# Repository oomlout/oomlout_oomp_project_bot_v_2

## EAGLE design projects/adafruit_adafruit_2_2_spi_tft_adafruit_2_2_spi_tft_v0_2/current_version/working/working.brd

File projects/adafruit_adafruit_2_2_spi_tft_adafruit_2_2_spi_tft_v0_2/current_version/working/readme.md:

# adafruit_2_2_spi_tft
 
## summary 
* id: adafruit_adafruit_2_2_spi_tft_adafruit_2_2_spi_tft_v0_2
* user: adafruit
* name: adafruit_2_2_spi_tft
* board: adafruit_2_2_spi_tft_v0_2
* repo: https://github.com/adafruit/Adafruit-2.2-SPI-TFT

* src_file_repo_sch: 
* src_file_repo_sch_link: https://github.com/adafruit/Adafruit-2.2-SPI-TFT/tree/master/
* full details link: https://github.com/oomlout/oomlout_oomp_project_bot_v_2/tree/main/projects/adafruit_adafruit_2_2_spi_tft_adafruit_2_2_spi_tft_v0_2/current_version/working  

## pcb  

[board (pdf)](working.pdf)

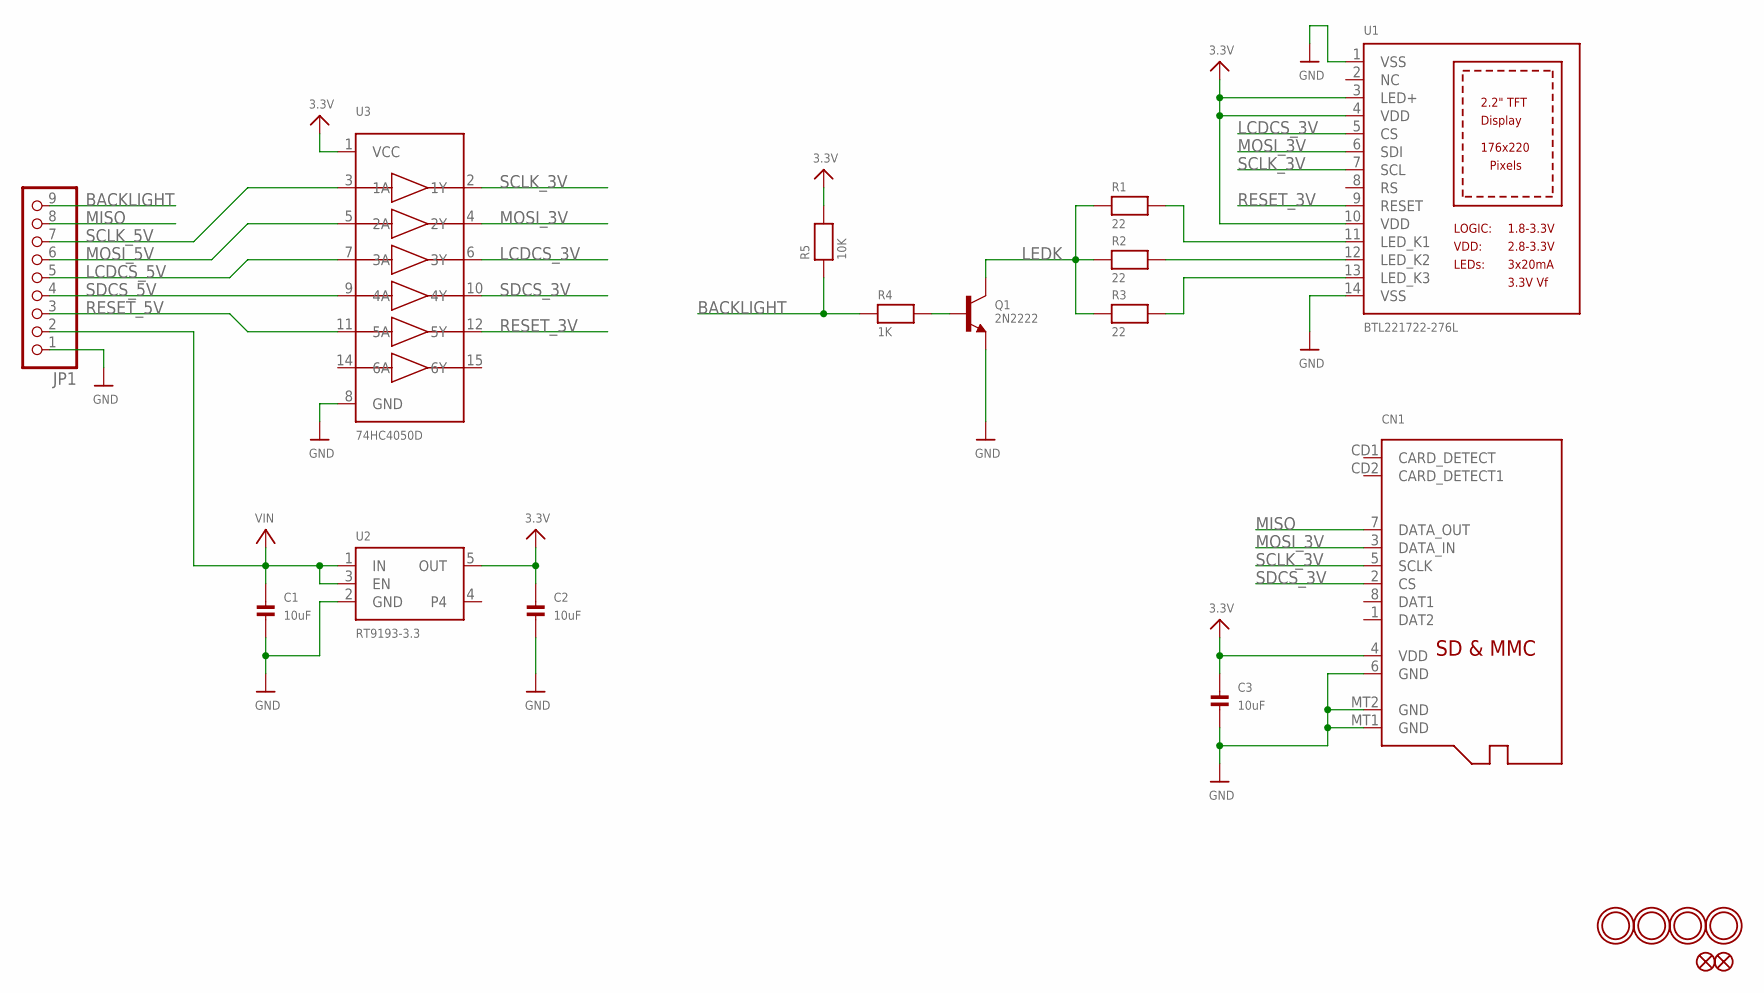
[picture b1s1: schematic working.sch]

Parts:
C1, C2, C3: 10uF; 0805
CN1: MICROSD
FID1, FID2: FIDUCIAL""; FIDUCIAL_1MM
JP1: HEADER-1X970MIL; 1X09_ROUND_70
Q1: 2N2222; SOT23-WIDE
R1, R2, R3: 22; 0805
R4: 1K; 0805
R5: 10K; 0805
U1: BTL221722-276L
U2: RT9193-3.3; SOT23-5
U3: 74HC4050D; SOIC16
U$2, U$3, U$4, U$5: MOUNTINGHOLE2.5; MOUNTINGHOLE_2.5_PLATED

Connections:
3.3V: C2.1, C3.1, CN1.4 (VDD), R5.2, U1.3 (LED+), U1.4 (VDD), U1.10 (VDD), U2.5 (OUT), U3.1 (VCC)
BACKLIGHT: JP1.9, R4.1, R5.1
GND: C1.2, C2.2, C3.2, CN1.6 (GND), CN1.MT1 (GND), CN1.MT2 (GND), JP1.1, Q1.2 (E), U1.1 (VSS), U1.14 (VSS), U2.2 (GND), U3.8 (GND)
LCDCS_3V: U1.5 (CS), U3.6 (3Y)
LCDCS_5V: JP1.5, U3.7 (3A)
LEDK: Q1.3 (C), R1.1, R2.1, R3.1
MISO: CN1.7 (DATA_OUT), JP1.8
MOSI_3V: CN1.3 (DATA_IN), U1.6 (SDI), U3.4 (2Y)
MOSI_5V: JP1.6, U3.5 (2A)
unnamed: R1.2, U1.11 (LED_K1)
unnamed: R2.2, U1.12 (LED_K2)
unnamed: R3.2, U1.13 (LED_K3)
unnamed: Q1.1 (B), R4.2
RESET_3V: U1.9 (RESET), U3.12 (5Y)
RESET_5V: JP1.3, U3.11 (5A)
SCLK_3V: CN1.5 (SCLK), U1.7 (SCL), U3.2 (1Y)
SCLK_5V: JP1.7, U3.3 (1A)
SDCS_3V: CN1.2 (CS), U3.10 (4Y)
SDCS_5V: JP1.4, U3.9 (4A)
VIN: C1.1, JP1.2, U2.1 (IN), U2.3 (EN)

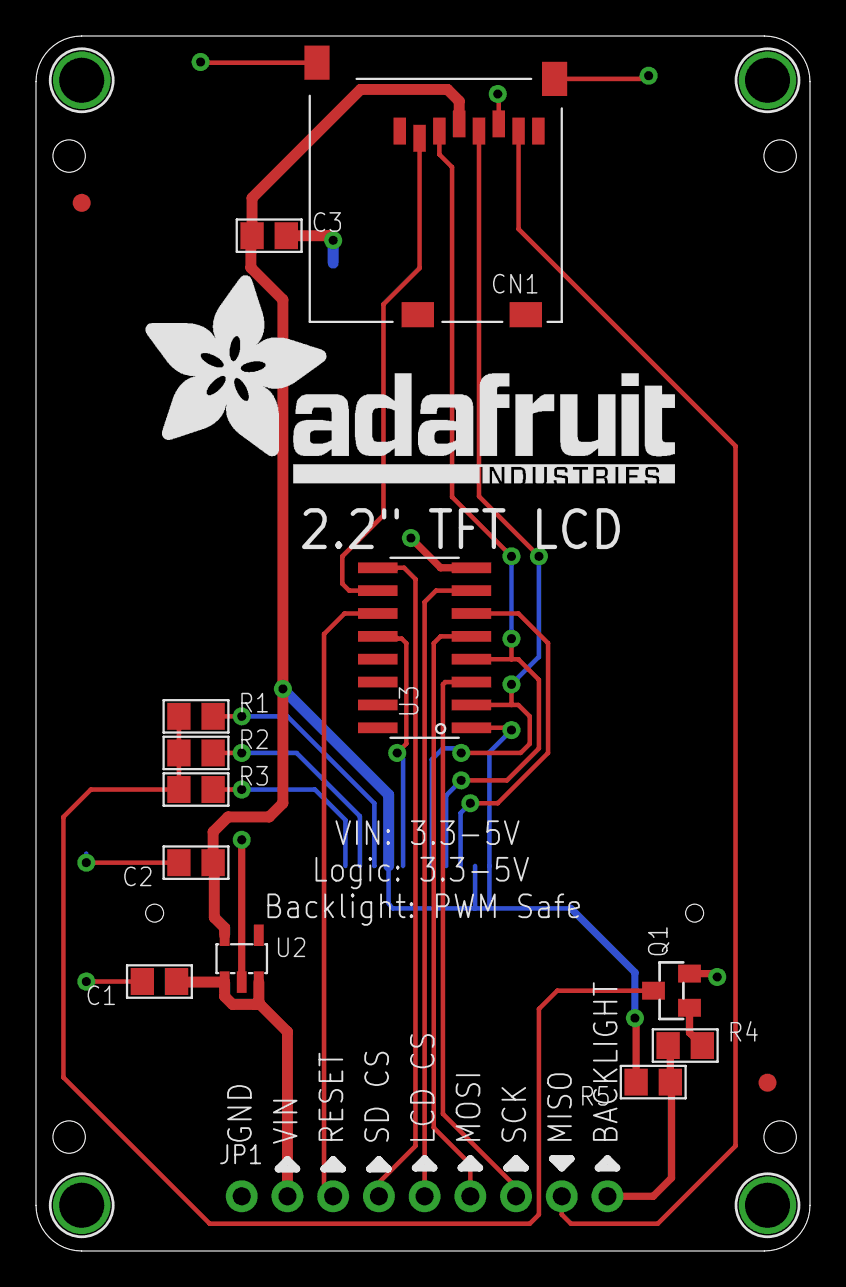
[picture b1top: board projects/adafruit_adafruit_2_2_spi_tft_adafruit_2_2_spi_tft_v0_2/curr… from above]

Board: 2 copper layers, 43.0 x 67.5 mm, 21 parts (1 on the bottom side), 20 nets.

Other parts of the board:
U$20: ADAFRUIT_TEXT_30MM

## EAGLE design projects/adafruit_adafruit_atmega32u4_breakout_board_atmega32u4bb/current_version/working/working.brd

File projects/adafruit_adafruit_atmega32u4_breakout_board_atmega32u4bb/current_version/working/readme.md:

# adafruit_atmega32u4_breakout_board
 
## summary 
* id: adafruit_adafruit_atmega32u4_breakout_board_atmega32u4bb
* user: adafruit
* name: adafruit_atmega32u4_breakout_board
* board: atmega32u4bb
* repo: https://github.com/adafruit/Adafruit_Atmega32u4_Breakout_Board

* src_file_repo_sch: 
* src_file_repo_sch_link: https://github.com/adafruit/Adafruit_Atmega32u4_Breakout_Board/tree/master/
* full details link: https://github.com/oomlout/oomlout_oomp_project_bot_v_2/tree/main/projects/adafruit_adafruit_atmega32u4_breakout_board_atmega32u4bb/current_version/working  

## pcb  

[board (pdf)](working.pdf)

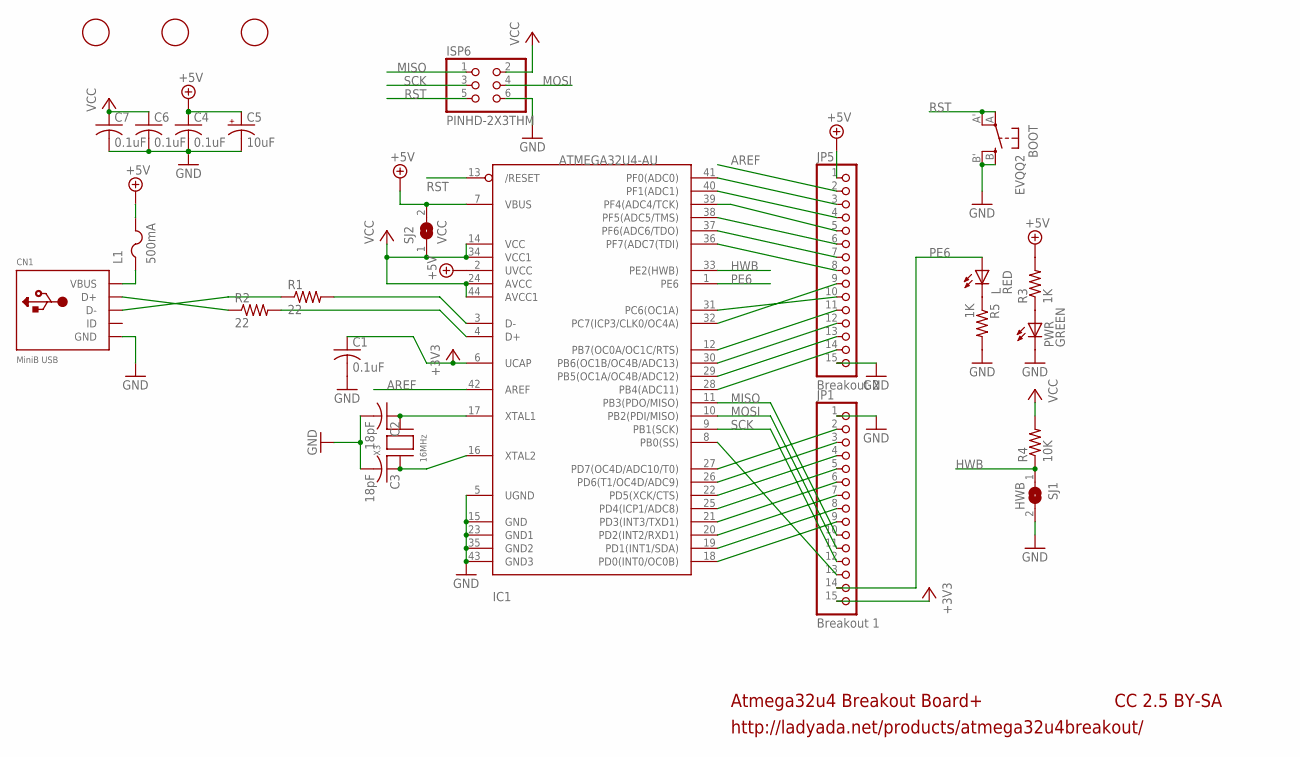
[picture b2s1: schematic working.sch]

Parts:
BOOT: EVQQ2; EVQ-Q2
C1, C4, C6, C7: 0.1uF; C0805K
C2, C3: 18pF; C0805K
C5: 10uF; A/3216-18R
CN1: MiniB USB; USB-MINIB
IC1: ATMEGA32U4-AU; TQFP44
ISP6: PINHD-2X3THM; ISP6
JP1: Breakout 1; 1X15-CB
JP5: Breakout 2; 1X15-CB
L: RED; CHIPLED_0805
L1: 500mA; R1206
PWR: GREEN; CHIPLED_0805
R1, R2: 22; R0805
R3, R5: 1K; R0805
R4: 10K; R0805
SJ1: HWB; SJ
SJ2: VCC; SJ
U$1, U$2, U$6: FIDUCIAL; FIDUCIAL_1MM
X3: 16MHz; NX5032

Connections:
+3V3: C1.1, IC1.6 (UCAP), JP1.15
+5V: C4.1, C5.+, IC1.2 (UVCC), IC1.7 (VBUS), JP5.1, L1.2, R3.2, SJ2.2
AREF: IC1.42 (AREF), JP5.2
GND: BOOT.B (S), BOOT.B' (S1), C1.2, C2.2, C3.2, C4.2, C5.-, C6.2, C7.2, CN1.GND, IC1.5 (UGND), IC1.15 (GND), IC1.23 (GND1), IC1.35 (GND2), IC1.43 (GND3), ISP6.6, JP1.1, JP5.15, PWR.C, R5.2, SJ1.2
HWB: IC1.33 (PE2(HWB)), R4.1, SJ1.1
MISO: IC1.11 (PB3(PDO/MISO)), ISP6.1, JP1.10
MOSI: IC1.10 (PB2(PDI/MISO)), ISP6.4, JP1.11
unnamed: PWR.A, R3.1
unnamed: CN1.D+, R2.1
unnamed: IC1.3 (D-), R1.2
unnamed: IC1.4 (D+), R2.2
unnamed: CN1.D-, R1.1
unnamed: C2.1, IC1.17 (XTAL1), X3.P$2
unnamed: C3.1, IC1.16 (XTAL2), X3.P$1
unnamed: L.C, R5.1
PB0: IC1.8 (PB0(SS)), JP1.13
PB4: IC1.28 (PB4(ADC11)), JP5.14
PB5: IC1.29 (PB5(OC1A/OC4B/ADC12)), JP5.13
PB6: IC1.30 (PB6(OC1B/OC4B/ADC13)), JP5.12
PB7: IC1.12 (PB7(OC0A/OC1C/RTS)), JP5.11
PC6: IC1.31 (PC6(OC1A)), JP5.10
PC7: IC1.32 (PC7(ICP3/CLK0/OC4A)), JP5.9
PD0: IC1.18 (PD0(INT0/OC0B)), JP1.9
PD1: IC1.19 (PD1(INT1/SDA)), JP1.8
PD2: IC1.20 (PD2(INT2/RXD1)), JP1.7
PD3: IC1.21 (PD3(INT3/TXD1)), JP1.6
PD4: IC1.25 (PD4(ICP1/ADC8)), JP1.5
PD5: IC1.22 (PD5(XCK/CTS)), JP1.4
PD6: IC1.26 (PD6(T1/OC4D/ADC9)), JP1.3
PD7: IC1.27 (PD7(OC4D/ADC10/T0)), JP1.2
PE6: IC1.1 (PE6), JP1.14, L.A
PF0: IC1.41 (PF0(ADC0)), JP5.3
PF1: IC1.40 (PF1(ADC1)), JP5.4
PF4: IC1.39 (PF4(ADC4/TCK)), JP5.5
PF5: IC1.38 (PF5(ADC5/TMS)), JP5.6
PF6: IC1.37 (PF6(ADC6/TDO)), JP5.7
PF7: IC1.36 (PF7(ADC7(TDI)), JP5.8
RST: BOOT.A, BOOT.A' (P1), IC1.13 (/RESET), ISP6.5
SCK: IC1.9 (PB1(SCK)), ISP6.3, JP1.12
VBUS: CN1.VBUS, L1.1
VCC: C6.1, C7.1, IC1.14 (VCC), IC1.24 (AVCC), IC1.34 (VCC1), IC1.44 (AVCC1), ISP6.2, R4.2, SJ2.1

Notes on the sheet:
Atmega32u4 Breakout Board+
http://ladyada.net/products/atmega32u4breakout/
CC 2.5 BY-SA

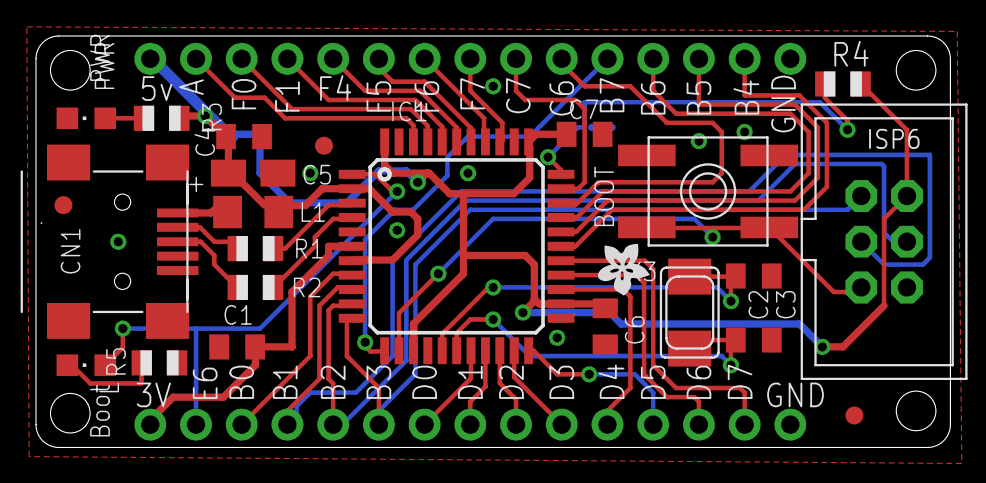
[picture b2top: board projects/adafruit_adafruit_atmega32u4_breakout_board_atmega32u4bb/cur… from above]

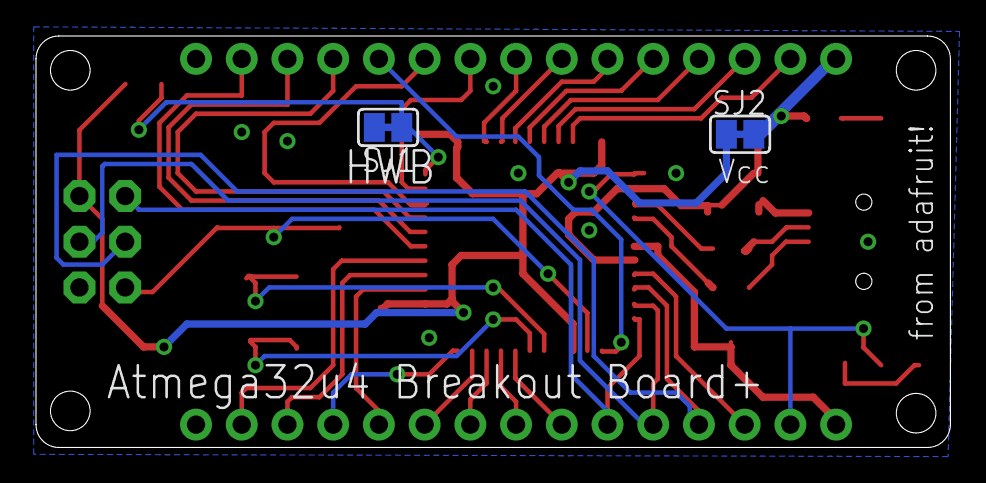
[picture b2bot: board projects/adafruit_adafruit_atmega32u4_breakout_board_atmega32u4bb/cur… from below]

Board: 2 copper layers, 50.8 x 22.9 mm, 28 parts (2 on the bottom side), 41 nets.

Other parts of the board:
U$4: ADAFRUIT200MIL

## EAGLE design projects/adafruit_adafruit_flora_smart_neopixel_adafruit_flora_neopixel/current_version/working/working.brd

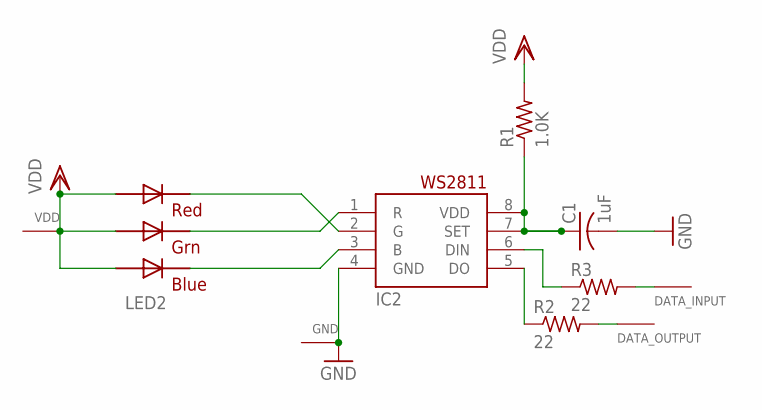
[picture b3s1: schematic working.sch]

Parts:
C1: 1uF; C0805K
DATA_INPUT: SEWTAP0.5IN; SEWINGTAP_0.5
DATA_OUTPUT: SEWTAP0.5IN; SEWINGTAP_0.5
GND: SEWTAP0.5IN; SEWINGTAP_0.5
IC2: WS2811-SOP8; SO08-SKINNYPADS
LED2: RGBLED5050
R1: 1.0K; R0805
R2, R3: 22; R0805
VDD: SEWTAP0.5IN; SEWINGTAP_0.5

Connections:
GND: C1.2, GND.TAP, IC2.4 (GND)
unnamed: IC2.3 (B), LED2.4 (BLUE_C)
unnamed: IC2.2 (G), LED2.5 (RED_C)
unnamed: IC2.1 (R), LED2.6 (GREEN_C)
unnamed: IC2.6 (DIN), R3.1
unnamed: IC2.5 (DO), R2.1
unnamed: DATA_INPUT.TAP, R3.2
unnamed: DATA_OUTPUT.TAP, R2.2
unnamed: C1.1, IC2.7 (SET), IC2.8 (VDD), R1.1
VDD: LED2.1 (GREEN_A), LED2.2 (RED_A), LED2.3 (BLUE_A), R1.2, VDD.TAP

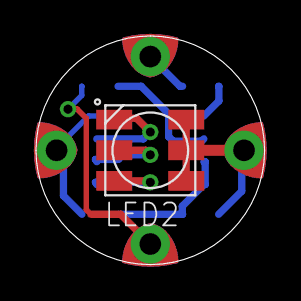
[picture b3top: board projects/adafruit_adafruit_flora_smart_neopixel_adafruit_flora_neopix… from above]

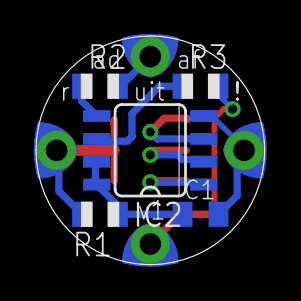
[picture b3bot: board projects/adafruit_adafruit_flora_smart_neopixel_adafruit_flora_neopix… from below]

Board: 2 copper layers, 12.7 x 12.7 mm, 10 parts (5 on the bottom side), 10 nets.

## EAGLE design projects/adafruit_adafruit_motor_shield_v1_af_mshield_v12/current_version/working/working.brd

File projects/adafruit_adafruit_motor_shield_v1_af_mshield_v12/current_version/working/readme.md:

# adafruit_motor_shield_v1
 
## summary 
* id: adafruit_adafruit_motor_shield_v1_af_mshield_v12
* user: adafruit
* name: adafruit_motor_shield_v1
* board: af_mshield_v12
* repo: https://github.com/adafruit/Adafruit_Motor-Shield-v1

* src_file_repo_sch: 
* src_file_repo_sch_link: https://github.com/adafruit/Adafruit_Motor-Shield-v1/tree/master/
* full details link: https://github.com/oomlout/oomlout_oomp_project_bot_v_2/tree/main/projects/adafruit_adafruit_motor_shield_v1_af_mshield_v12/current_version/working  

## schematic  
  
[schematic (pdf)](working_schematic.pdf) 

## pcb  

[board (pdf)](working.pdf)  

## bom_schematic
no data

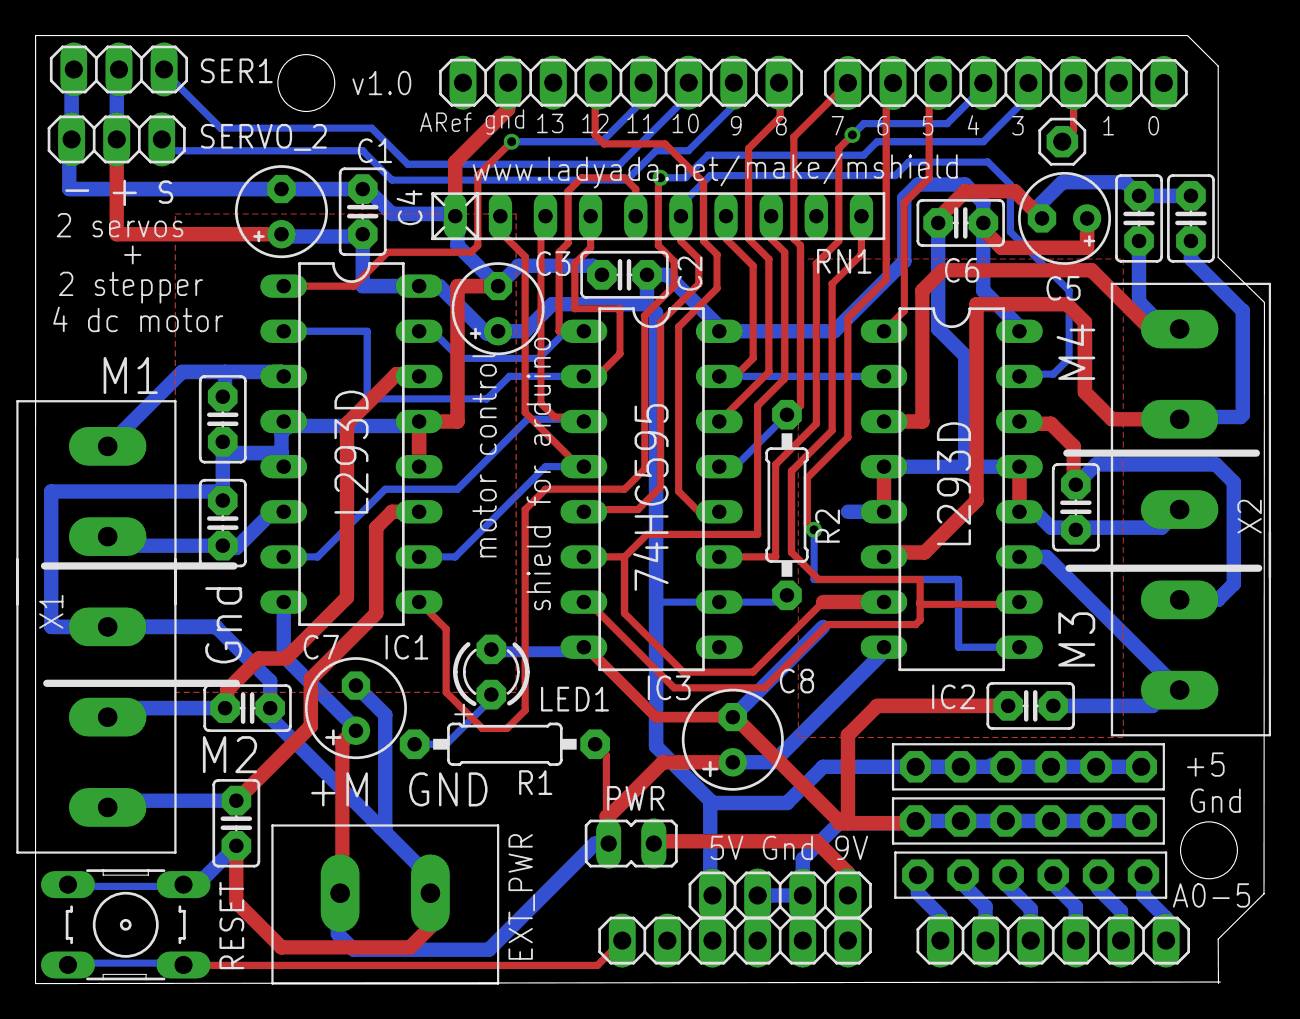
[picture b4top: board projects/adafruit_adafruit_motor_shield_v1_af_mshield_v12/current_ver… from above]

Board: 2 copper layers, 69.2 x 53.4 mm, 39 parts (0 on the bottom side), 39 nets.

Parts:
C1, C3, C5: 100uF/6V; E2,5-5
C2, C4, C10, C11, C12, C13, C20, C21, C22, C23: 0.1uF; C025-025X050
C6: C025-025X050
C7, C8: 100uF/16V; E2,5-6
EXT_PWR: PINHEAD; TERMBLOCK508
IC1, IC2: DIL16
IC3: 74HCT595N; DIL16
J1, J3: 1X08
JP1, JP2: 1X06
JP3: 1X01
JP4: 1X04
JP5, JP8, JP10: 1X06-BIG
LED1: LED3MM
PWR: JP1
R1: 0207/10
R2: 10k; 0207/10
RESET: Reset; B3F-10XX
RN1: RN-10
SER1: 1X03
SERVO_2: 1X03
X1, X2: TERM5; TERM1X5

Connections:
9V: JP1.6, JP4.4, PWR.1
DIR_CLK: IC3.11, J1.5
DIR_EN: IC3.13, J1.8, R2.2
DIR_LATCH: IC3.12, J3.5
DIR_SER: IC3.14, J3.1
GND: C1.-, C2.2, C3.-, C4.2, C5.-, C6.2, C7.-, C8.-, C10.2, C11.2, C12.2, C13.2, C20.2, C21.2, C22.2, C23.2, EXT_PWR.P$4, IC1.4, IC1.5, IC1.12, IC1.13, IC2.4, IC2.5, IC2.12, IC2.13, IC3.8, J3.7, JP1.4, JP1.5, JP4.2, JP4.3, JP10.1, JP10.2, JP10.3, JP10.4, JP10.5, JP10.6, LED1.K, RESET.1, RESET.2, RN1.1, SER1.3, SERVO_2.3, X1.P3, X2.P3
M1A: IC1.2, IC3.2, RN1.4
M1B: IC1.7, IC3.3, RN1.3
M2A: IC1.15, IC3.1, RN1.5
M2B: IC1.10, IC3.4, RN1.2
M3A: IC2.2, IC3.15, RN1.7
M3B: IC2.7, IC3.6, RN1.8
M4A: IC2.15, IC3.5, RN1.6
M4B: IC2.10, IC3.7, RN1.10
unnamed: C13.1, IC1.3, X1.P1
unnamed: JP2.1, JP5.1
unnamed: JP2.2, JP5.2
unnamed: JP2.3, JP5.3
unnamed: JP2.4, JP5.4
unnamed: JP2.5, JP5.5
unnamed: C23.1, IC2.3, X2.P5
unnamed: C22.1, IC2.6, X2.P4
unnamed: C20.1, IC2.11, X2.P1
unnamed: J1.3, JP3.1
unnamed: JP2.6, JP5.6
unnamed: C21.1, IC2.14, X2.P2
unnamed: C12.1, IC1.6, X1.P2
unnamed: C10.1, IC1.11, X1.P5
unnamed: C11.1, IC1.14, X1.P4
unnamed: LED1.A, R1.1
PWM0A: IC2.9, J1.7
PWM0B: IC2.1, J1.6
PWM1A: J3.2, SERVO_2.1
PWM1B: J3.3, SER1.1
PWM2A: IC1.1, J3.4
PWM2B: IC1.9, J1.4
RESET: JP1.1, RESET.3, RESET.4
V+: C7.+, C8.+, EXT_PWR.P$3, IC1.8, IC2.8, PWR.2, R1.2
VCC: C1.+, C2.1, C3.+, C4.1, C5.+, C6.1, IC1.16, IC2.16, IC3.10, IC3.16, JP1.3, JP4.1, JP8.1, JP8.2, JP8.3, JP8.4, JP8.5, JP8.6, R2.1, SER1.2, SERVO_2.2

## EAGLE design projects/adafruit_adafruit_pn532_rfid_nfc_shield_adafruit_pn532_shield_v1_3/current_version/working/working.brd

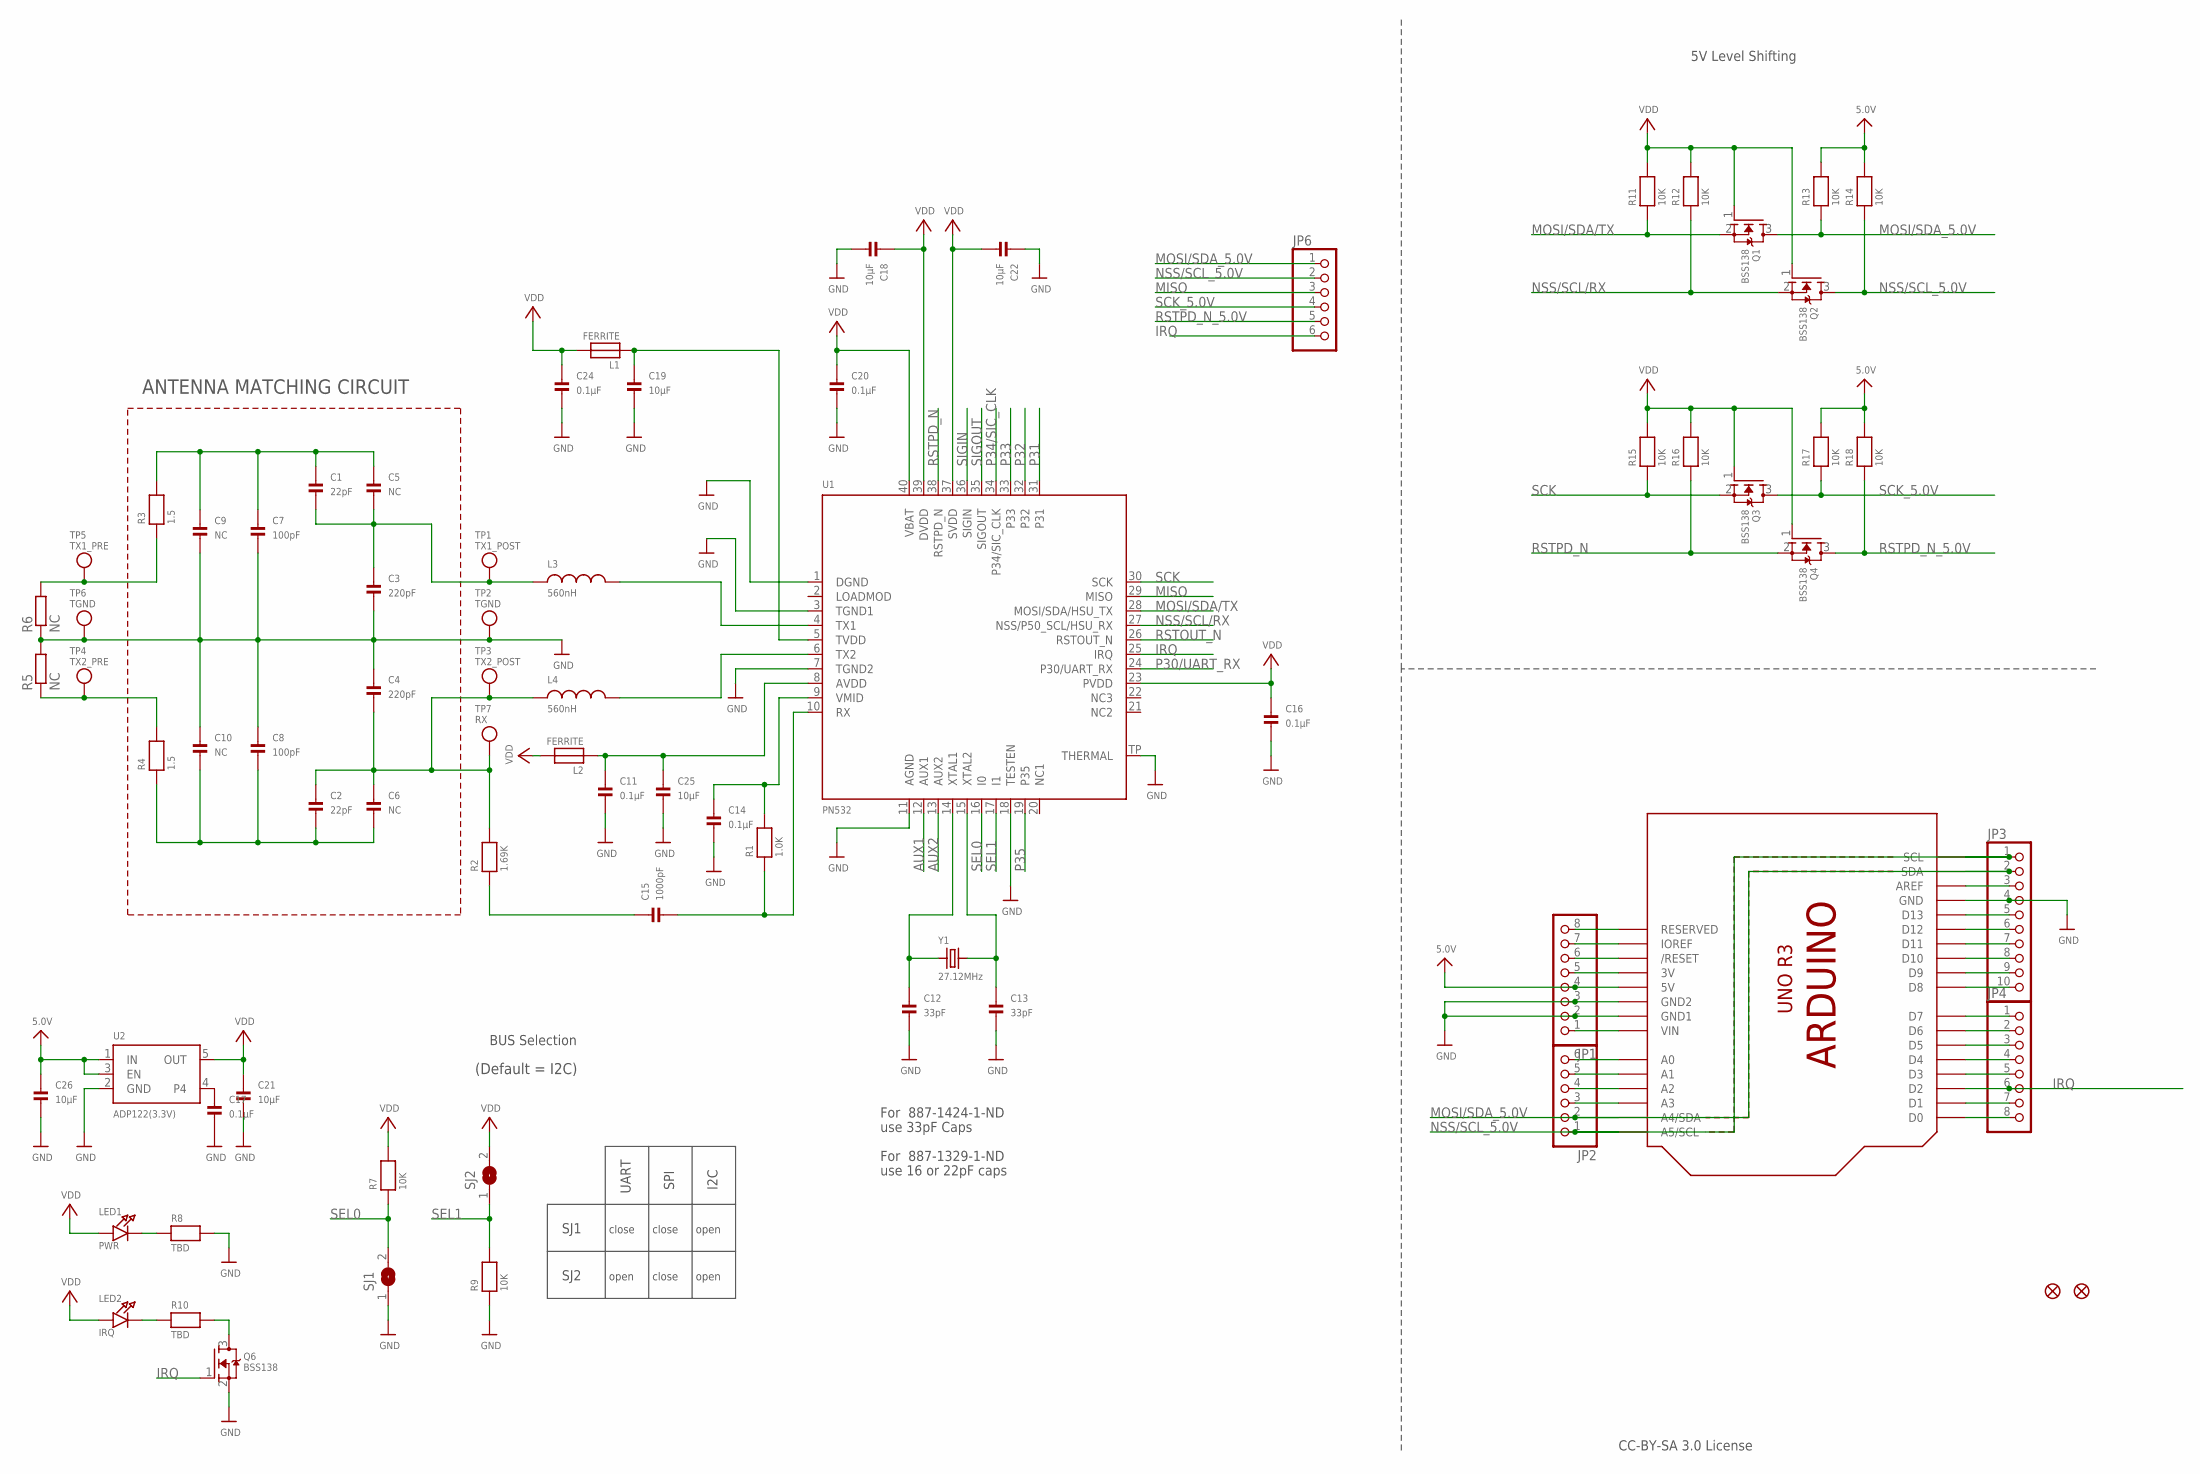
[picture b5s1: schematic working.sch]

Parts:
C1, C2: 22pF; 0805
C3, C4: 220pF; 0805
C5, C6, C9, C10: NC; 0805
C7, C8: 100pF; 0805
C11, C14, C16, C17, C20, C24: 0.1µF; 0805
C12, C13: 33pF; 0805
C15: 1000pF; 0805
C18, C19, C21, C22, C25, C26: 10µF; 0805
FID1, FID2: FIDUCIAL1X2.5; FIDUCIAL-1X2.5
JP1, JP4: HEADER-1X870MIL; 1X08_ROUND_70
JP2: HEADER-1X670MIL; 1X06_ROUND_70
JP3: HEADER-1X1070MIL; 1X10_ROUND70
JP6: PINHD-1X6B; 1X06-BIG
L1, L2: FERRITE; 0805
L3, L4: 560nH; 0805
LED1: PWR; CHIPLED_0805
LED2: IRQ; CHIPLED_0805
Q1, Q2, Q3, Q4, Q6: BSS138; SOT23-WIDE
R1: 1.0K; 0805
R2: 1.69K; 0805
R3, R4: 1.5; 0805
R5, R6: NC; R0201
R7, R9, R11, R12, R13, R14, R15, R16, R17, R18: 10K; 0805
R8, R10: TBD; 0805
SJ1, SJ2: SOLDERJUMPERREFLOW_NOPASTE; SOLDERJUMPER_REFLOW_NOPASTE
TP1: TX1_POST; TESTPOINT_PAD_2MM
TP2, TP6: TGND; TESTPOINT_PAD_2MM
TP3: TX2_POST; TESTPOINT_PAD_2MM
TP4: TX2_PRE; TESTPOINT_PAD_2MM
TP5: TX1_PRE; TESTPOINT_PAD_2MM
TP7: RX; TESTPOINT_PAD_2MM
U1: PN532; HVQFN40-6X6
U2: ADP122(3.3V); SOT23-5
U3: ARDUINOR3NODIM; ARDUINOR3-NODIM
Y1: 27.12MHz; CRYSTAL_3.2X2.5

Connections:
5.0V: C26.1, JP1.4, R13.2, R14.2, R17.2, R18.2, U2.1 (IN), U2.3 (EN), U3.5V
AUX1: U1.12 (AUX1)
AUX2: U1.13 (AUX2)
GND: C3.2, C4.1, C7.2, C8.1, C9.2, C10.1, C11.2, C12.2, C13.2, C14.2, C16.2, C17.2, C18.2, C19.2, C20.2, C21.2, C22.1, C24.2, C25.2, C26.2, JP1.2, JP1.3, JP3.4, Q6.2 (S), R5.2, R6.1, R8.2, R9.1, SJ1.1, TP2.P$1, TP6.P$1, U1.1 (DGND), U1.3 (TGND1), U1.7 (TGND2), U1.11 (AGND), U1.18 (TESTEN), U1.TP (THERMAL), U2.2 (GND), U3.GND, U3.GND1, U3.GND2
IRQ: JP4.6, JP6.6, Q6.1 (G), U1.25 (IRQ), U3.D2
MISO: JP6.3, U1.29 (MISO)
MOSI/SDA/TX: Q1.2 (S), R11.1, U1.28 (MOSI/SDA/HSU_TX)
MOSI/SDA_5.0V: JP2.2, JP3.2, JP6.1, Q1.3 (D), R13.1, U3.A4 (A4/SDA), U3.SDA
unnamed: L3.2, U1.4 (TX1)
unnamed: L4.2, U1.6 (TX2)
unnamed: C1.2, C3.1, C5.2, L3.1, TP1.P$1
unnamed: R3.1, R6.2, TP5.P$1
unnamed: R4.2, R5.1, TP4.P$1
unnamed: LED1.C, R8.1
unnamed: C12.1, U1.14 (XTAL1), Y1.1
unnamed: C13.1, U1.15 (XTAL2), Y1.2
unnamed: C15.1, R2.1
unnamed: C14.1, R1.2, U1.9 (VMID)
unnamed: C15.2, R1.1, U1.10 (RX)
unnamed: C2.1, C4.2, C6.1, L4.1, R2.2, TP3.P$1, TP7.P$1
unnamed: C11.1, C25.1, L2.1, U1.8 (AVDD)
unnamed: C19.1, L1.1, U1.5 (TVDD)
unnamed: JP1.1, U3.VIN
unnamed: JP1.5, U3.3V
unnamed: JP1.6, U3.RESET (/RESET)
unnamed: JP1.7, U3.IOREF
unnamed: JP1.8, U3.RESERVED
unnamed: JP2.3, U3.A3
unnamed: JP2.4, U3.A2
unnamed: JP2.5, U3.A1
unnamed: JP2.6, U3.A0
unnamed: JP3.3, U3.AREF
unnamed: JP3.5, U3.D13
unnamed: JP3.6, U3.D12
unnamed: JP3.7, U3.D11
unnamed: JP3.8, U3.D10
unnamed: JP3.9, U3.D9
unnamed: JP3.10, U3.D8
unnamed: JP4.1, U3.D7
unnamed: JP4.2, U3.D6
unnamed: JP4.3, U3.D5
unnamed: JP4.4, U3.D4
unnamed: JP4.5, U3.D3
unnamed: LED2.C, R10.1
unnamed: JP4.7, U3.D1
unnamed: JP4.8, U3.D0
unnamed: Q6.3 (D), R10.2
unnamed: C17.1, U2.4
NSS/SCL/RX: Q2.2 (S), R12.1, U1.27 (NSS/P50_SCL/HSU_RX)
NSS/SCL_5.0V: JP2.1, JP3.1, JP6.2, Q2.3 (D), R14.1, U3.A5 (A5/SCL), U3.SCL
P30/UART_RX: U1.24 (P30/UART_RX)
P31: U1.31
P32: U1.32
P33: U1.33
P34/SIC_CLK: U1.34 (P34/SIC_CLK)
P35: U1.19 (P35)
RSTOUT_N: U1.26 (RSTOUT_N)
RSTPD_N: Q4.2 (S), R16.1, U1.38 (RSTPD_N)
RSTPD_N_5.0V: JP6.5, Q4.3 (D), R18.1
SCK: Q3.2 (S), R15.1, U1.30 (SCK)
SCK_5.0V: JP6.4, Q3.3 (D), R17.1
SEL0: R7.1, SJ1.2, U1.16 (I0)
SEL1: R9.2, SJ2.1, U1.17 (I1)
SIGIN: U1.36 (SIGIN)
SIGOUT: U1.35 (SIGOUT)
TX1_ANTENNA: C1.1, C5.1, C7.1, C9.1, R3.2
TX2_ANTENNA: C2.2, C6.2, C8.2, C10.2, R4.1
VDD: C16.1, C18.1, C20.1, C21.1, C22.2, C24.1, L1.2, L2.2, LED1.A, LED2.A, Q1.1 (G), Q2.1 (G), Q3.1 (G), Q4.1 (G), R7.2, R11.2, R12.2, R15.2, R16.2, SJ2.2, U1.23 (PVDD), U1.37 (SVDD), U1.39 (DVDD), U1.40 (VBAT), U2.5 (OUT)

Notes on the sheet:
ANTENNA MATCHING CIRCUIT
SJ1
SJ2
UART
SPI
I2C
close
open
CC-BY-SA 3.0 License
For 887-1329-1-ND
use 16 or 22pF caps
For 887-1424-1-ND
use 33pF Caps
BUS Selection
(Default = I2C)
5V Level Shifting

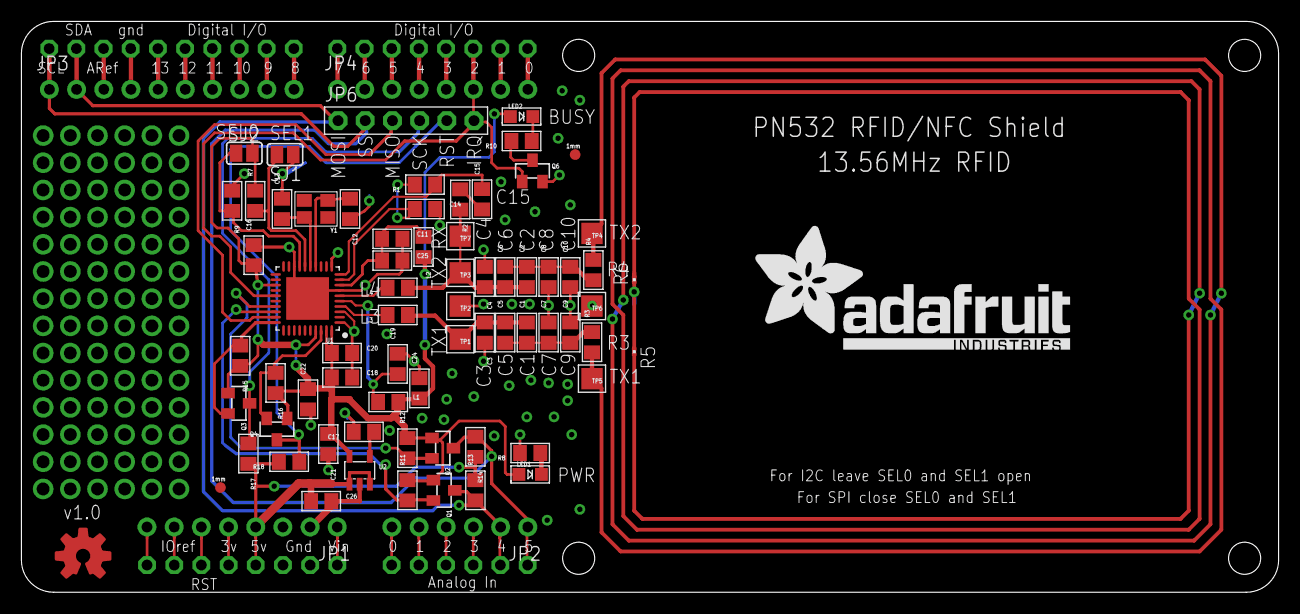
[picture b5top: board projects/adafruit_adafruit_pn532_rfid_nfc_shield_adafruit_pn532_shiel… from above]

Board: 2 copper layers, 117.5 x 53.3 mm, 76 parts (0 on the bottom side), 57 nets.

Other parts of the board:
U$3: ADAFRUIT_TEXT_30MM
U$50: OSHWLOGO_TOP_0.2

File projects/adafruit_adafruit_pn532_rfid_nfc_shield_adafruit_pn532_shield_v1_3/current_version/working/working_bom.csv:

"Id";"Designator";"Footprint";"Quantity";"Designation";"Supplier and ref";
1;"C7,C8";"0805";2;"100pF";;;
2;"Q2,Q6,Q4,Q1,Q3";"SOT23-WIDE";5;"BSS138";;;
3;"L4,L3";"0805";2;"560nH";;;
4;"R7,R16,R14,R9,R17,R13,R15,R18,R12,R11";"0805";10;"10K";;;
5;"JP6";"1X06-BIG";1;"";;;
6;"@HOLE1,@HOLE0,@HOLE2,@HOLE3";"";4;"";;;
7;"C14,C20,C11,C17,C24,C16";"0805";6;"0.1µF";;;
8;"JP1,JP4";"1X08_ROUND_70";2;"";;;
9;"C21,C22,C25,C18,C19,C26";"0805";6;"10µF";;;
10;"R10,R8";"0805";2;"TBD";;;
11;"TP6,TP2";"TESTPOINT_PAD_2MM";2;"TGND";;;
12;"R6,R5";"R0201";2;"NC";;;
13;"U$50";"OSHWLOGO_TOP_0.2";1;"";;;
14;"L1,L2";"0805";2;"FERRITE";;;
15;"C10,C6,C5,C9";"0805";4;"NC";;;
16;"JP3";"1X10_ROUND70";1;"";;;
17;"TP3";"TESTPOINT_PAD_2MM";1;"TX2_POST";;;
18;"C1,C2";"0805";2;"22pF";;;
19;"C3,C4";"0805";2;"220pF";;;
20;"JP2";"1X06_ROUND_70";1;"";;;
21;"LED2";"CHIPLED_0805";1;"IRQ";;;
22;"FID2,FID1";"FIDUCIAL-1X2.5";2;"FIDUCIAL1X2.5";;;
23;"TP4";"TESTPOINT_PAD_2MM";1;"TX2_PRE";;;
24;"C15";"0805";1;"1000pF";;;
25;"TP5";"TESTPOINT_PAD_2MM";1;"TX1_PRE";;;
26;"U1";"HVQFN40-6X6";1;"PN532";;;
27;"Y1";"CRYSTAL_3.2X2.5";1;"27.12MHz";;;
28;"SJ1,SJ2";"SOLDERJUMPER_REFLOW_NOPASTE";2;"";;;
29;"C12,C13";"0805";2;"33pF";;;
30;"U$3";"ADAFRUIT_TEXT_30MM";1;"";;;
31;"LED1";"CHIPLED_0805";1;"PWR";;;
32;"TP1";"TESTPOINT_PAD_2MM";1;"TX1_POST";;;
33;"R2";"0805";1;"1.69K";;;
34;"R4,R3";"0805";2;"1.5";;;
35;"TP7";"TESTPOINT_PAD_2MM";1;"RX";;;
36;"R1";"0805";1;"1.0K";;;
37;"U3";"ARDUINOR3-NODIM";1;"ARDUINOR3NODIM";;;
38;"U2";"SOT23-5";1;"ADP122(3.3V)";;;

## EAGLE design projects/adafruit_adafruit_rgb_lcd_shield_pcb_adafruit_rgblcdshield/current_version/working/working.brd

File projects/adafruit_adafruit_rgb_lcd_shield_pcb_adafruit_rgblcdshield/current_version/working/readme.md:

# adafruit_rgb_lcd_shield_pcb
 
## summary 
* id: adafruit_adafruit_rgb_lcd_shield_pcb_adafruit_rgblcdshield
* user: adafruit
* name: adafruit_rgb_lcd_shield_pcb
* board: adafruit_rgblcdshield
* repo: https://github.com/adafruit/Adafruit-RGB-LCD-shield-PCB

* src_file_repo_sch: 
* src_file_repo_sch_link: https://github.com/adafruit/Adafruit-RGB-LCD-shield-PCB/tree/master/
* full details link: https://github.com/oomlout/oomlout_oomp_project_bot_v_2/tree/main/projects/adafruit_adafruit_rgb_lcd_shield_pcb_adafruit_rgblcdshield/current_version/working  

## pcb  

[board (pdf)](working.pdf)

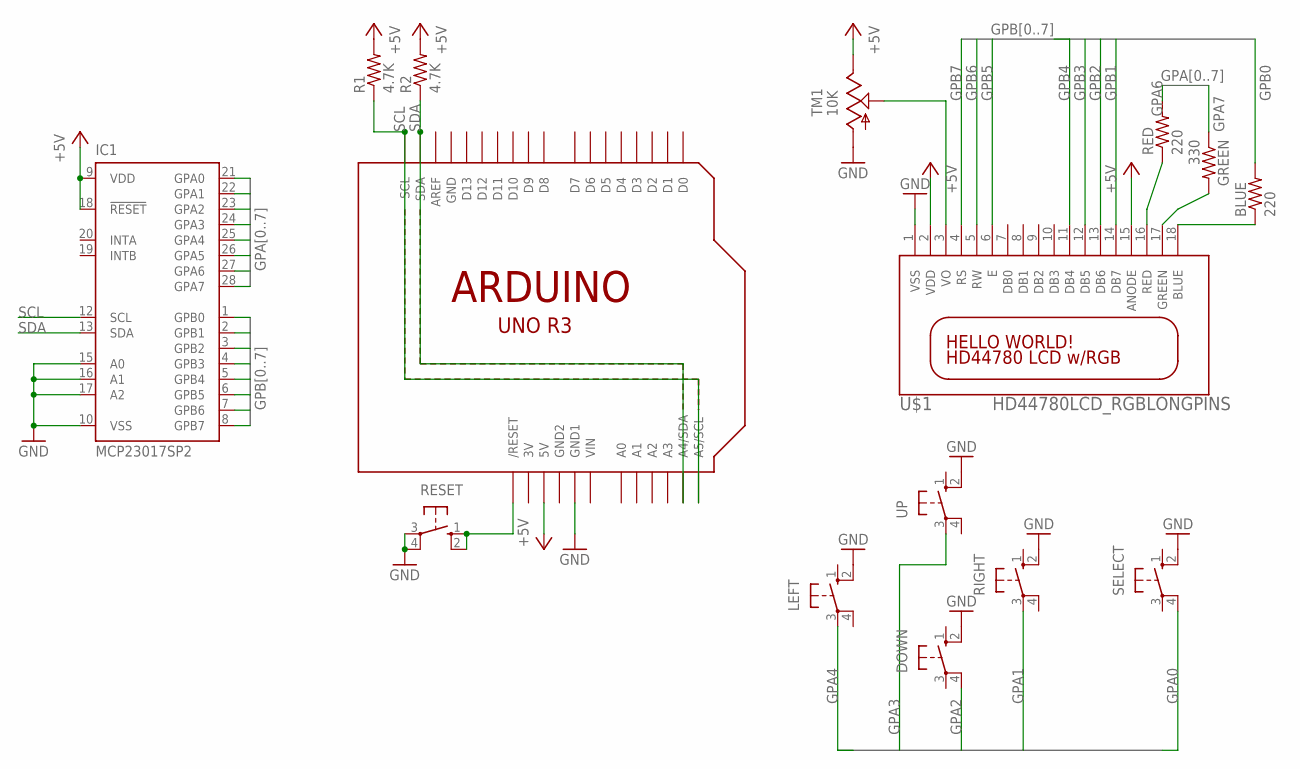
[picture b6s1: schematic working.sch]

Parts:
BLUE: 220; 0207/10
DOWN: 10-XX; B3F-10XX
GREEN: 330; 0207/10
IC1: MCP23017SP2; DIL28-3-ROUND
LEFT: 10-XX; B3F-10XX
R1, R2: 4.7K; 0207/10
RED: 220; 0207/10
RESET: 10-XX; B3F-10XX
RIGHT: 10-XX; B3F-10XX
SELECT: 10-XX; B3F-10XX
TM1: 10K; 6MM
U1: ARDUINOR3-NOIOREF-NOTEXT; ARDUINOR3-NOTEXT-NOIOREF
U$1: HD44780LCD_RGBLONGPINS; LCD1602-RGB
UP: 10-XX; B3F-10XX

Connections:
3V: U1.3V
+5V: IC1.9 (VDD), IC1.18 (!RESET), R1.2, R2.2, TM1.E, U1.5V, U$1.2 (VDD), U$1.15 (ANODE)
GND: DOWN.2 (S1), IC1.10 (VSS), IC1.15 (A0), IC1.16 (A1), IC1.17 (A2), LEFT.2 (S1), RESET.3, RESET.4 (P1), RIGHT.2 (S1), SELECT.2 (S1), TM1.A, U1.GND, U1.GND1, U$1.1 (VSS), UP.2 (S1)
GND2: U1.GND2
GPA0: IC1.21 (GPA0), SELECT.4 (P1)
GPA1: IC1.22 (GPA1), RIGHT.3
GPA2: DOWN.4 (P1), IC1.23 (GPA2)
GPA3: IC1.24 (GPA3), UP.3
GPA4: IC1.25 (GPA4), LEFT.3
GPA5: IC1.26 (GPA5)
GPA6: IC1.27 (GPA6), RED.2
GPA7: GREEN.1, IC1.28 (GPA7)
GPB0: BLUE.2, IC1.1 (GPB0)
GPB1: IC1.2 (GPB1), U$1.14 (DB7)
GPB2: IC1.3 (GPB2), U$1.13 (DB6)
GPB3: IC1.4 (GPB3), U$1.12 (DB5)
GPB4: IC1.5 (GPB4), U$1.11 (DB4)
GPB5: IC1.6 (GPB5), U$1.6 (E)
GPB6: IC1.7 (GPB6), U$1.5 (RW)
GPB7: IC1.8 (GPB7), U$1.4 (RS)
unnamed: BLUE.1, U$1.18 (BLUE)
unnamed: GREEN.2, U$1.17 (GREEN)
unnamed: RED.1, U$1.16 (RED)
unnamed: TM1.S, U$1.3 (VO)
unnamed: RESET.1 (S), RESET.2 (S1), U1.RESET (/RESET)
SCL: IC1.12 (SCL), R1.1, U1.A5 (A5/SCL), U1.SCL
SDA: IC1.13 (SDA), R2.1, U1.A4 (A4/SDA), U1.SDA
VIN: U1.VIN

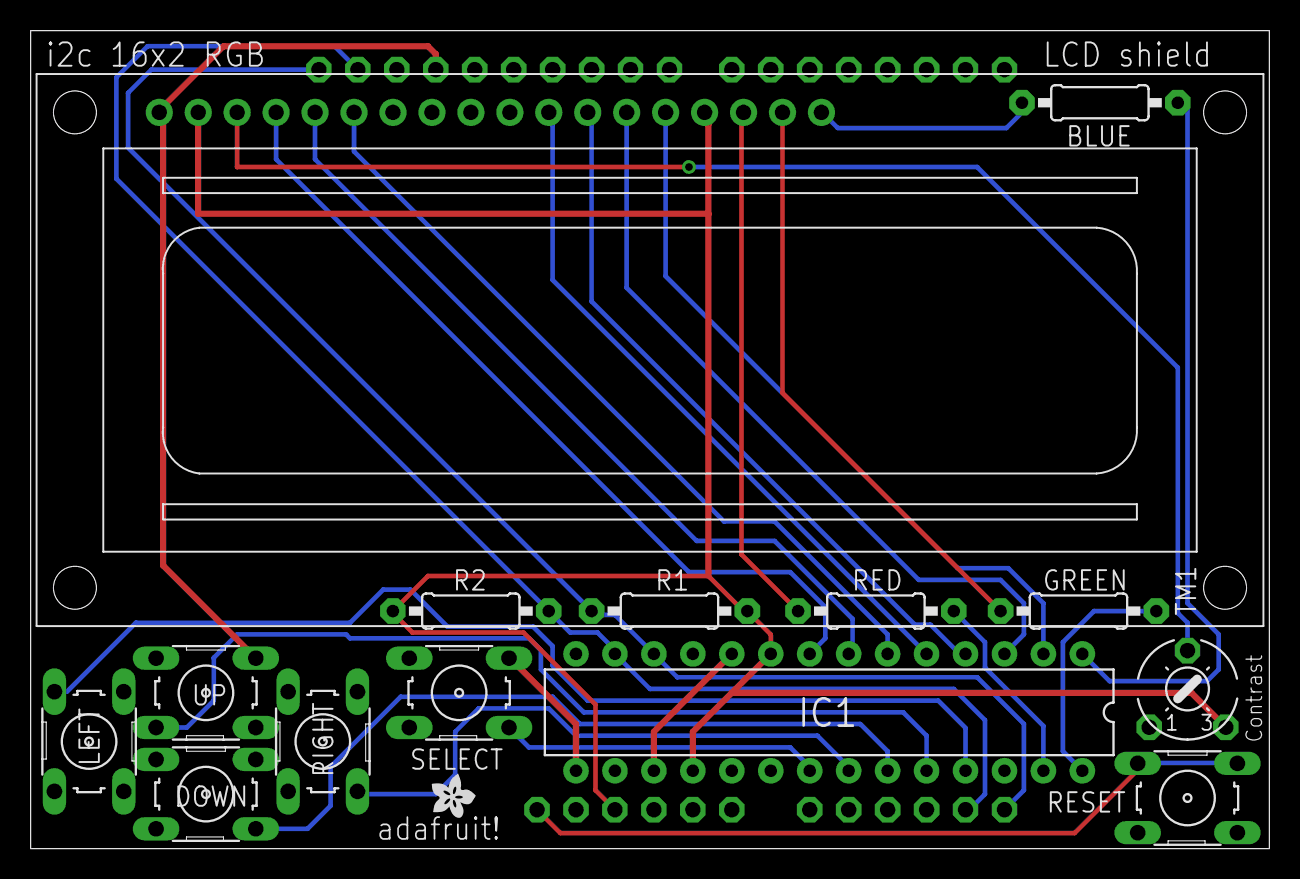
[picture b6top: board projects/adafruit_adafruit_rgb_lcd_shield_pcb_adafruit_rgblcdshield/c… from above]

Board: 2 copper layers, 80.8 x 53.3 mm, 16 parts (0 on the bottom side), 24 nets.

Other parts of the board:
U$2: ADAFRUIT200MIL
